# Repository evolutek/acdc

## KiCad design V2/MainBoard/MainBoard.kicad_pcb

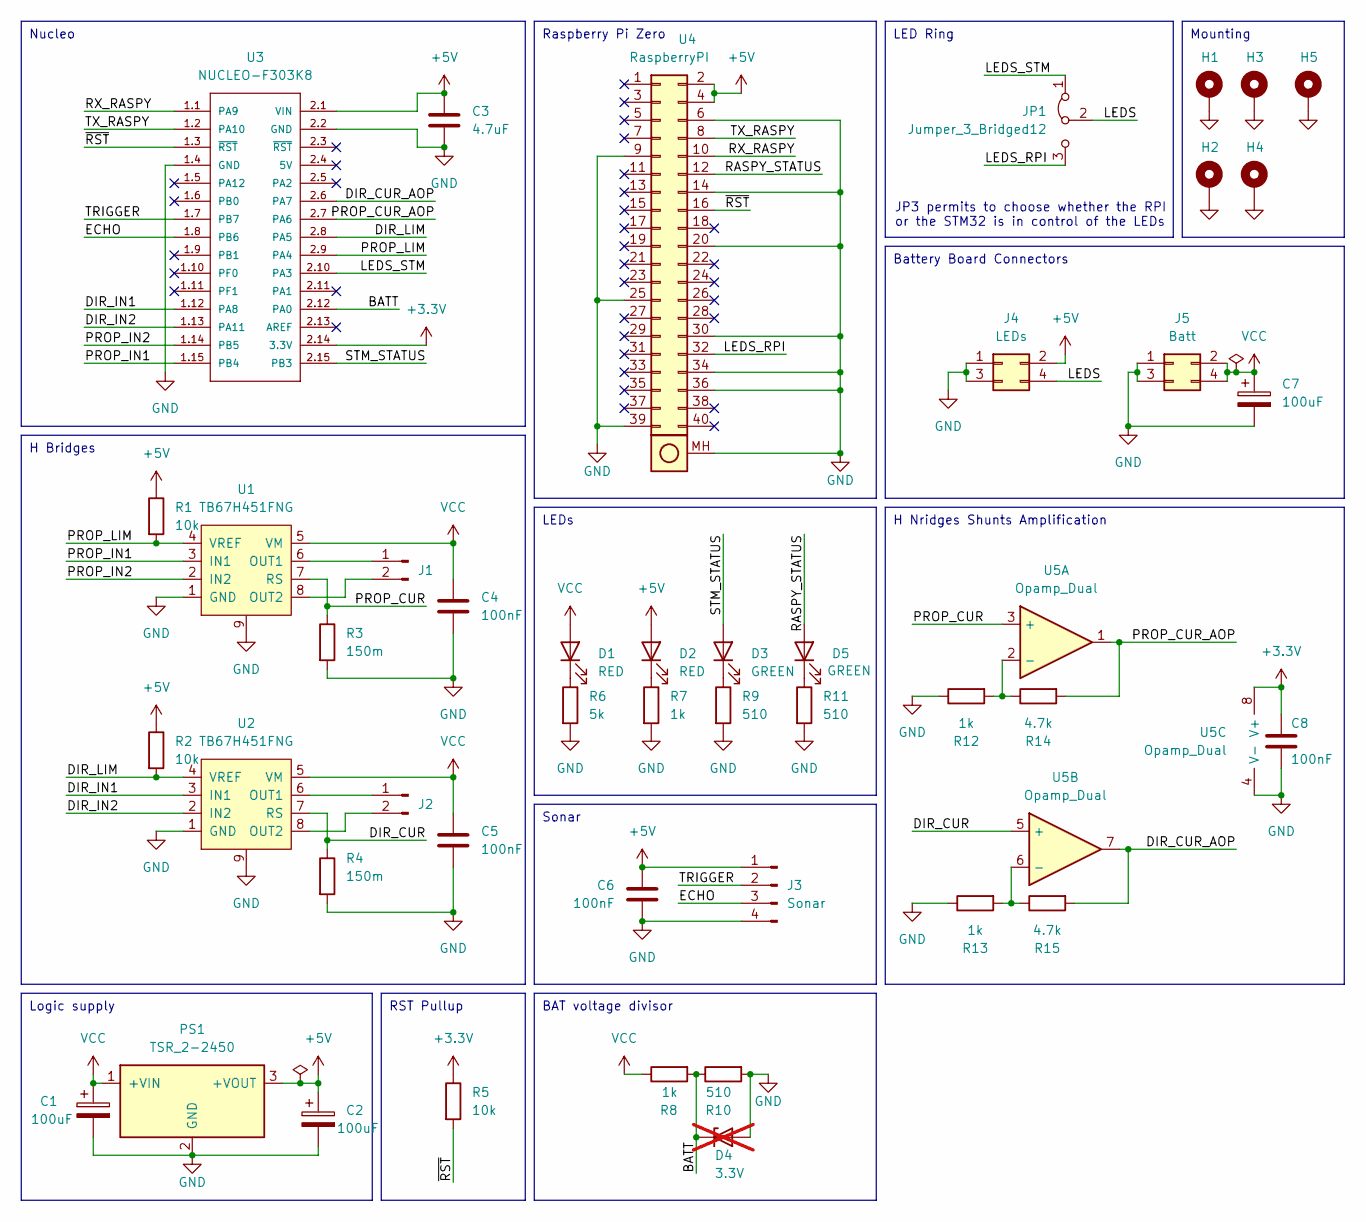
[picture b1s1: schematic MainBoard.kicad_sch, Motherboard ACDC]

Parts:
C1, C7: 100uF; C_Elec_6.3x5.4
C2: 100uF; CP_Elec_6.3x7.7
C3: 4.7uF; C_0603_1608Metric
C4, C5, C6, C8: 100nF; C_0603_1608Metric
D1, D2: RED; LED_0805_2012Metric
D3, D5: GREEN; LED_0805_2012Metric
D4: 3.3V; D_SOD-523; not fitted
H1, H2, H3, H4: MountingHole_Pad; MountingHole_2.5mm_Pad_Via
H5: MountingHole_Pad; WA-SMSI_9774110360
J1, J2: Conn_01x02_Pin; JST_PH_S2B-PH-K_1x02_P2.00mm_Horizontal
J3: Sonar; PinHeader_1x04_P2.54mm_Vertical
J4: LEDs; PinSocket_2x02_P2.54mm_Vertical_SMD
J5: Batt; PinSocket_2x02_P2.54mm_Vertical_SMD
JP1: Jumper_3_Bridged12; PinHeader_1x03_P2.54mm_Vertical
PS1: TSR_2-2450
R1, R2, R5: 10k; R_0603_1608Metric
R3, R4: 150m; R_0805_2012Metric
R6: 5k; R_0603_1608Metric
R7, R8, R12, R13: 1k; R_0603_1608Metric
R9, R10, R11: 510; R_0603_1608Metric
R14, R15: 4.7k; R_0603_1608Metric
U1, U2: TB67H451FNG; HSOP-8-1EP_3.9x4.9mm_P1.27mm_EP2.41x3.1mm_ThermalVias
U3: NUCLEO-F303K8; MODULE_NUCLEO-F303K8
U4: RaspberryPI; Shield_Raspberry_Pi_Zero_W
U5: Opamp_Dual; SOIC-8_3.9x4.9mm_P1.27mm

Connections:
+3.3V: C8.1, R5.1, U3.2.14 (3.3V), U5.8 (V+)
+5V: C2.1, C3.1, C6.1, D2.2 (A), J3.1, J4.2, PS1.3 (+VOUT), R1.1, R2.1, U3.2.1 (VIN), U4.2, U4.4
/BATT: D4.1 (K), R8.2, R10.1, U3.2.12 (PA0)
/DIR_CUR: R4.1, U2.7 (RS), U5.5 (+)
/DIR_CUR_AOP: R15.2, U3.2.6 (PA7), U5.7
/DIR_IN1: U2.3 (IN1), U3.1.12 (PA8)
/DIR_IN2: U2.2 (IN2), U3.1.13 (PA11)
/DIR_LIM: R2.2, U2.4 (VREF), U3.2.8 (PA5)
/ECHO: J3.3, U3.1.8 (PB6)
/LEDS: J4.4, JP1.2 (C)
/LEDS_RPI: JP1.3 (B), U4.32
/LEDS_STM: JP1.1 (A), U3.2.10 (PA3)
/PROP_CUR: R3.1, U1.7 (RS), U5.3 (+)
/PROP_CUR_AOP: R14.2, U3.2.7 (PA6), U5.1
/PROP_IN1: U1.3 (IN1), U3.1.15 (PB4)
/PROP_IN2: U1.2 (IN2), U3.1.14 (PB5)
/PROP_LIM: R1.2, U1.4 (VREF), U3.2.9 (PA4)
/RASPY_STATUS: D5.2 (A), U4.12
/RX_RASPY: U3.1.1 (PA9), U4.10
/STM_STATUS: D3.2 (A), U3.2.15 (PB3)
/TRIGGER: J3.2, U3.1.7 (PB7)
/TX_RASPY: U3.1.2 (PA10), U4.8
/~RST: R5.2, U3.1.3 (~RST), U4.16
GND: C1.2, C2.2, C3.2, C4.2, C5.2, C6.2, C7.2, C8.2, D4.2 (A), H1.1, H2.1, H3.1, H4.1, H5.1, J3.4, J4.1, J4.3, J5.1, J5.3, PS1.2 (GND), R3.2, R4.2, R6.2, R7.2, R9.2, R10.2, R11.2, R12.1, R13.1, U1.1 (GND), U1.9, U2.1 (GND), U2.9, U3.1.4 (GND), U3.2.2 (GND), U4.6, U4.9, U4.14, U4.20, U4.25, U4.30, U4.34, U4.36, U4.39, U4.MH (MountingHoles), U5.4 (V-)
unnamed: D1.1 (K), R6.1
unnamed: D2.1 (K), R7.1
unnamed: D3.1 (K), R9.1
unnamed: D5.1 (K), R11.1
unnamed: J1.1, U1.6 (OUT1)
unnamed: J1.2, U1.8 (OUT2)
unnamed: J2.1, U2.6 (OUT1)
unnamed: J2.2, U2.8 (OUT2)
unnamed: R12.2, R14.1, U5.2 (-)
unnamed: R13.2, R15.1, U5.6 (-)
VCC: C1.1, C4.1, C5.1, C7.1, D1.2 (A), J5.2, J5.4, PS1.1 (+VIN), R8.1, U1.5 (VM), U2.5 (VM)

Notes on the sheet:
Battery Board Connectors
H Bridges
Sonar
Raspberry Pi Zero
Mounting
H Nridges Shunts Amplification
Nucleo
BAT voltage divisor
LED Ring
LEDs
Logic supply
RST Pullup
JP3 permits to choose whether the RPI or the STM32 is in control of the LEDs

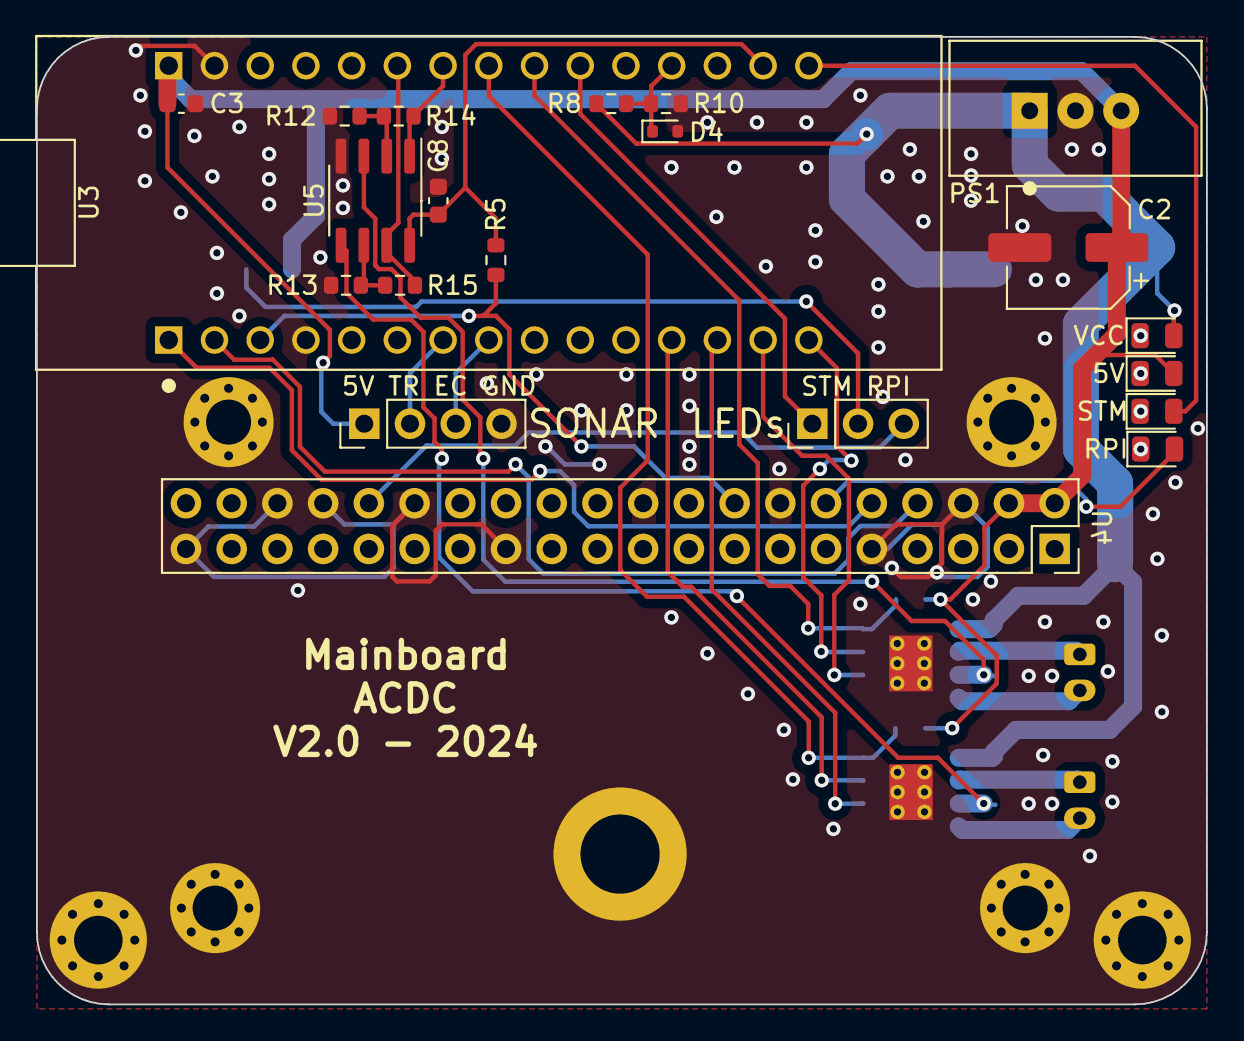
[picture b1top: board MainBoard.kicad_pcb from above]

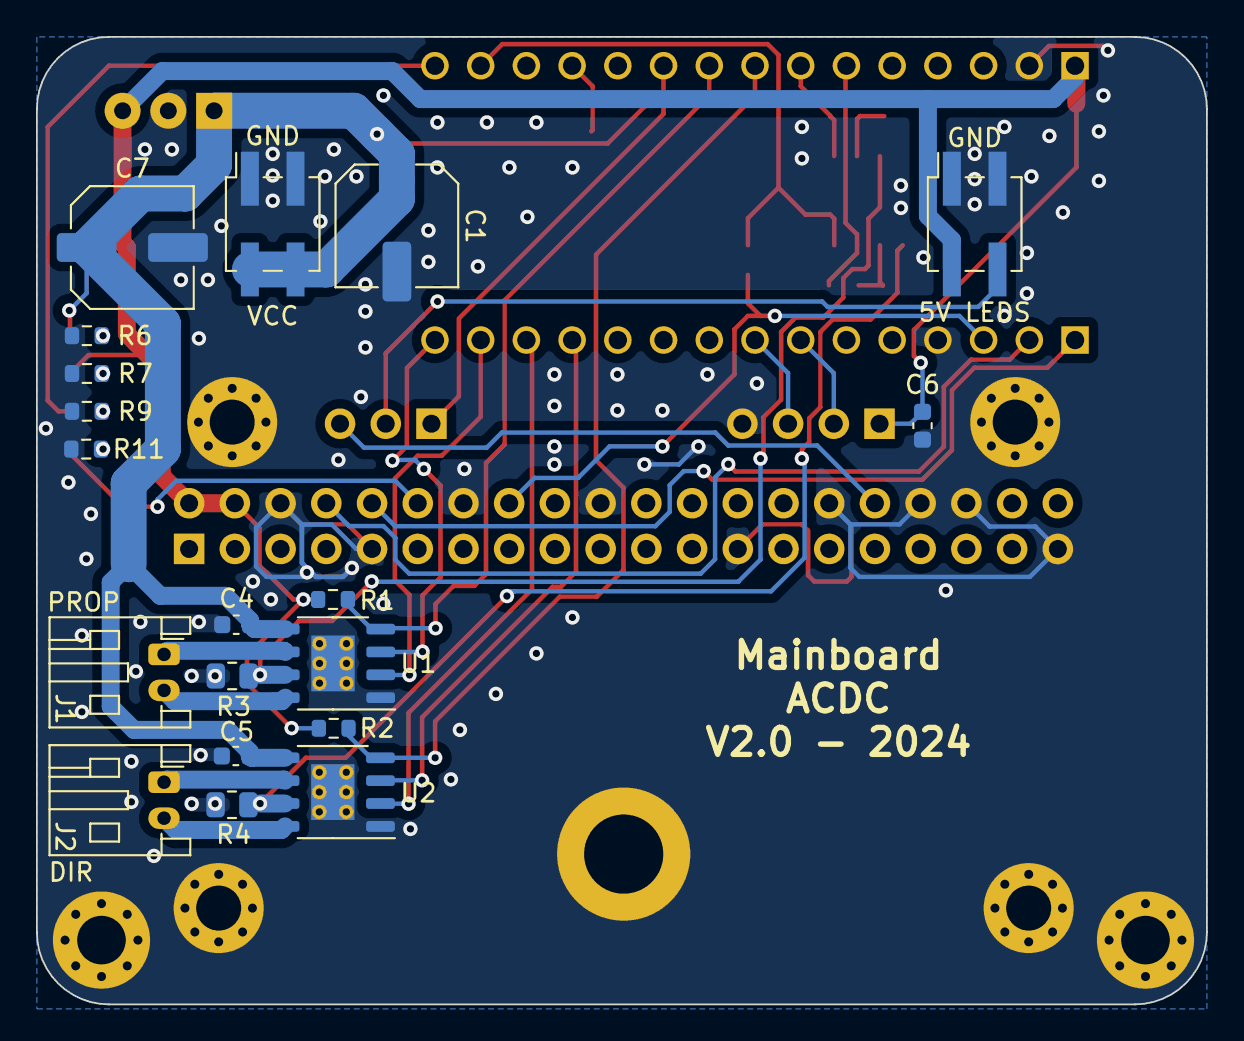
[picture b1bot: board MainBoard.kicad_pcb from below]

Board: 2 copper layers, 65.0 x 53.8 mm, 45 parts (21 on the bottom side), 35 nets.

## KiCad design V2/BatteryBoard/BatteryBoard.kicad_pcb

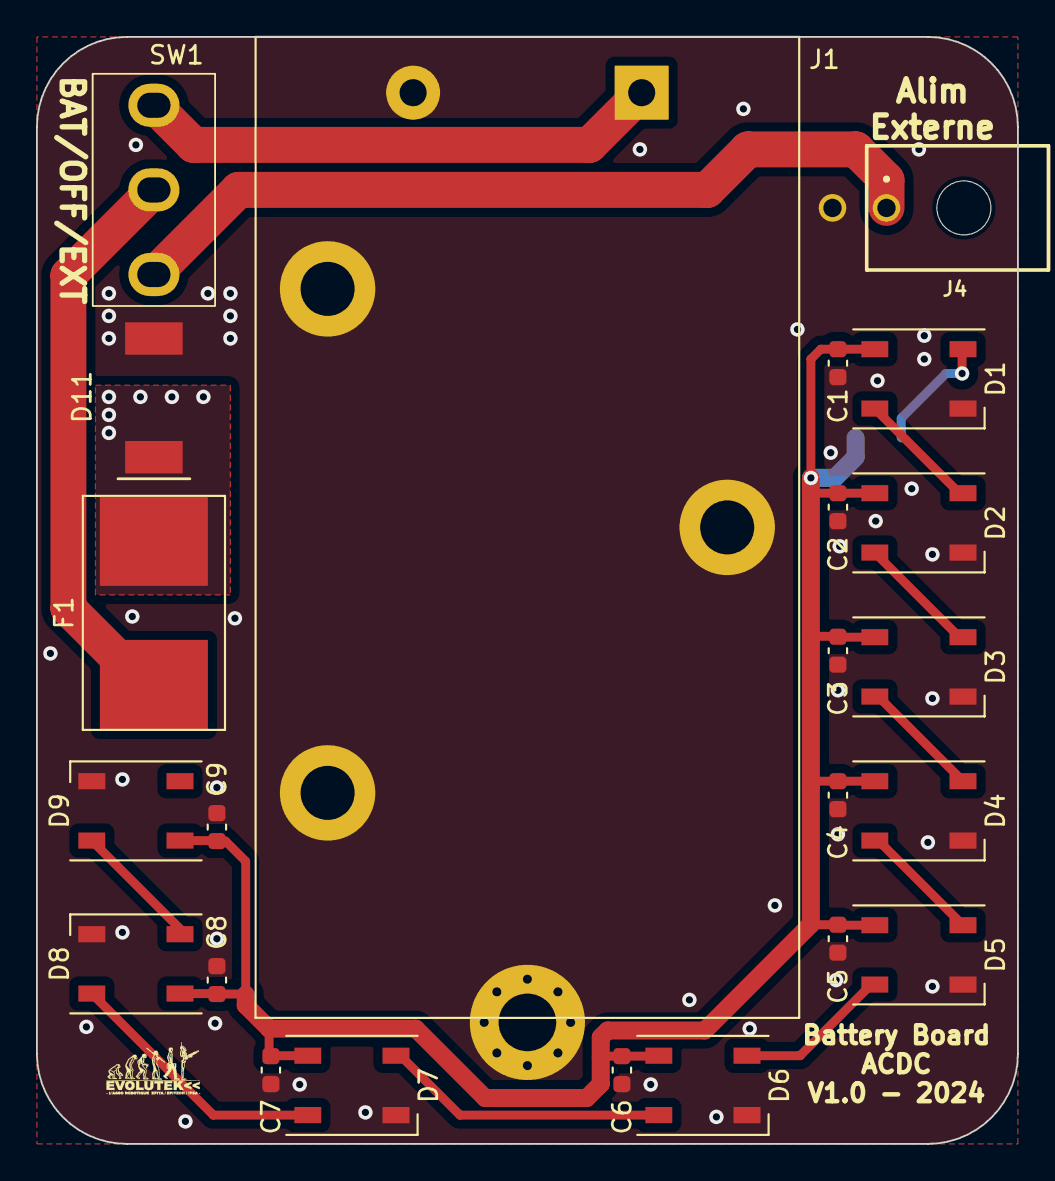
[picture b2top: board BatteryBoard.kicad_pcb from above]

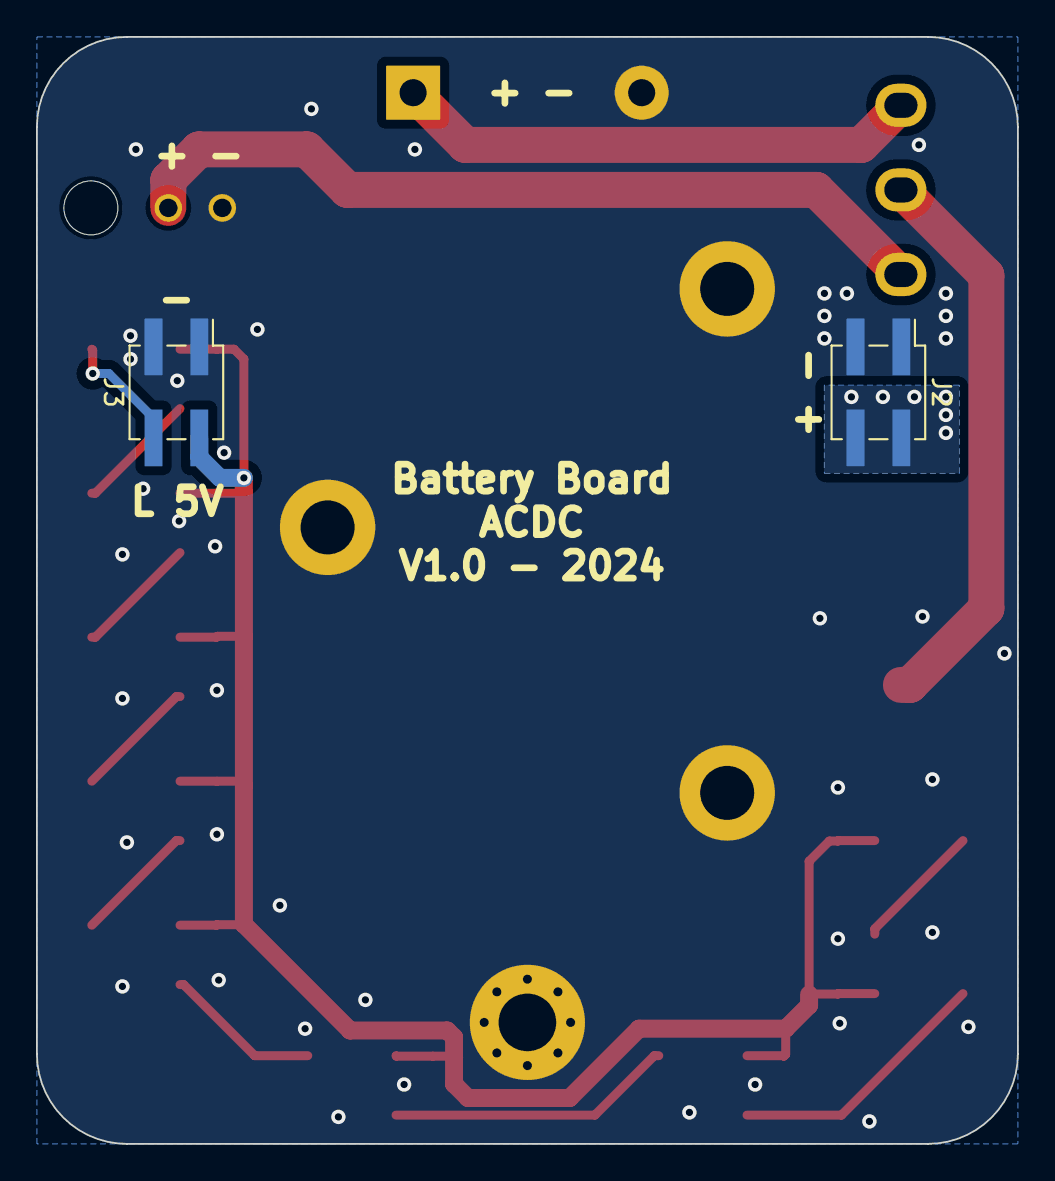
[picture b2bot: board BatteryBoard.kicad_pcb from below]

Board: 2 copper layers, 54.5 x 61.5 mm, 26 parts (2 on the bottom side), 15 nets.

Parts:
C1, C2, C3, C4, C5, C6, C7, C8, C9: 100nF; C_0603_1608Metric
D1, D2, D3, D4, D5, D6, D7, D8, D9: WS2812B; LED_WS2812B_PLCC4_5.0x5.0mm_P3.2mm
D11: D; DO-214AB
F1: Fuse; 0031.7701.11
H1: MountingHole_Pad; MountingHole_3.2mm_M3_Pad_Via
J1: 9V Battery; BatteryHolder_Eagle_12BH611-GR-Modified
J2, J3: Conn_02x02_Odd_Even; PinHeader_2x02_P2.54mm_Vertical_SMD
J4: Aux Alim; 66200221022
SW1: SW_SPDT_MSM; Power Switch RS SPDT

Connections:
+5V: C1.1, C2.1, C3.1, C4.1, C5.1, C6.1, C7.1, C8.1, C9.1, D1.1 (VDD), D2.1 (VDD), D3.1 (VDD), D4.1 (VDD), D5.1 (VDD), D6.1 (VDD), D7.1 (VDD), D8.1 (VDD), D9.1 (VDD), J3.2
/LEDS: D1.4 (DIN), J3.4
/LEDS_LTR: D5.2 (DOUT), D6.4 (DIN)
GND: C1.2, C2.2, C3.2, C4.2, C5.2, C6.2, C7.2, C8.2, C9.2, D1.3 (VSS), D2.3 (VSS), D3.3 (VSS), D4.3 (VSS), D5.3 (VSS), D6.3 (VSS), D7.3 (VSS), D8.3 (VSS), D9.3 (VSS), D11.2 (A), H1.1, J1.2, J1.MP (MountPin), J2.1, J2.3, J3.1, J3.3, J4.2
unnamed: D1.2 (DOUT), D2.4 (DIN)
unnamed: D2.2 (DOUT), D3.4 (DIN)
unnamed: D3.2 (DOUT), D4.4 (DIN)
unnamed: D4.2 (DOUT), D5.4 (DIN)
unnamed: D6.2 (DOUT), D7.4 (DIN)
unnamed: D7.2 (DOUT), D8.4 (DIN)
unnamed: D8.2 (DOUT), D9.4 (DIN)
unnamed: F1.1, SW1.2
unnamed: J1.1, SW1.3
unnamed: J4.1, SW1.1
VCC: D11.1 (K), F1.2, J2.2, J2.4

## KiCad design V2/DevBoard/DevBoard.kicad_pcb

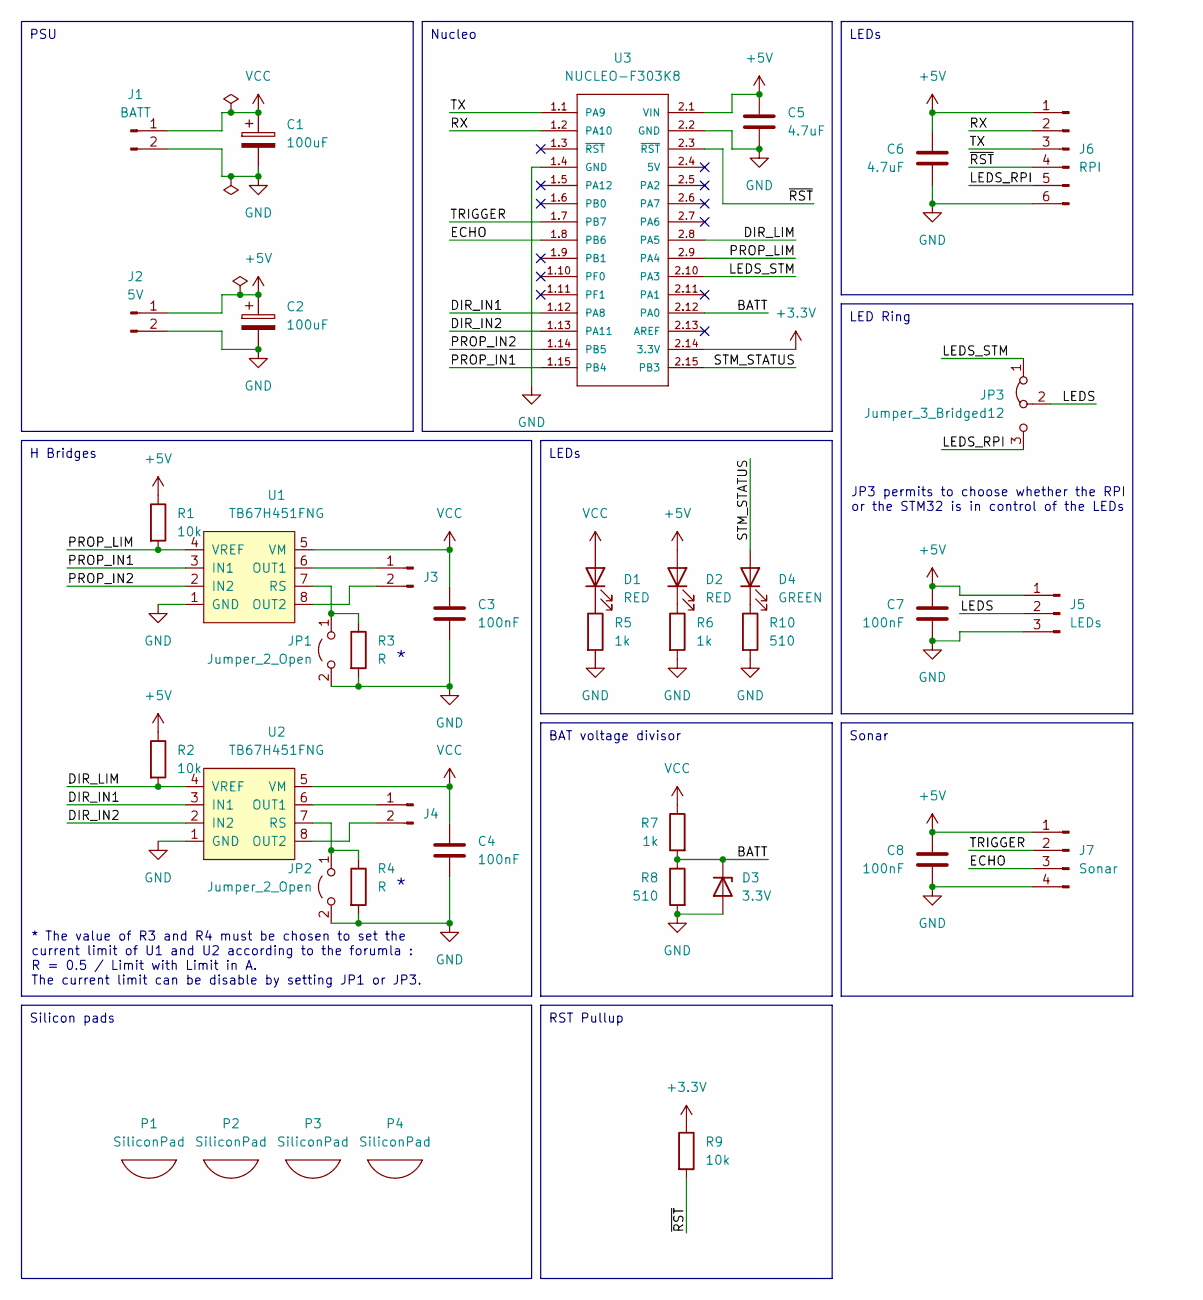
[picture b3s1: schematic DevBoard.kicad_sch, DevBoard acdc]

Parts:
C1, C2: 100uF; CP_Elec_6.3x7.7
C3, C4, C7, C8: 100nF; C_0603_1608Metric
C5, C6: 4.7uF; C_0603_1608Metric
D1, D2: RED; LED_0805_2012Metric
D3: 3.3V; D_SOD-523
D4: GREEN; LED_0805_2012Metric
J1: BATT; 66200221022
J2: 5V; 66200221022
J3, J4: Conn_01x02_Pin; PinHeader_1x02_P2.54mm_Vertical
J5: LEDs; PinHeader_1x03_P2.54mm_Vertical
J6: RPI; PinHeader_1x06_P2.54mm_Vertical
J7: Sonar; PinHeader_1x04_P2.54mm_Vertical
JP1, JP2: Jumper_2_Open; SolderJumper-2_P1.3mm_Open_TrianglePad1.0x1.5mm
JP3: Jumper_3_Bridged12; PinHeader_1x03_P2.54mm_Vertical
P1, P2, P3, P4: SiliconPad; Silicon Pad 6x2mm
R1, R2, R9: 10k; R_0603_1608Metric
R3, R4: R; R_0603_1608Metric
R5, R6, R7: 1k; R_0603_1608Metric
R8, R10: 510; R_0603_1608Metric
U1, U2: TB67H451FNG; HSOP-8-1EP_3.9x4.9mm_P1.27mm_EP2.41x3.1mm_ThermalVias
U3: NUCLEO-F303K8; MODULE_NUCLEO-F303K8

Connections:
+3.3V: R9.1, U3.2.14 (3.3V)
+5V: C2.1, C5.1, C6.1, C7.1, C8.1, D2.2 (A), J2.1, J5.1, J6.1, J7.1, R1.1, R2.1, U3.2.1 (VIN)
/BATT: D3.1 (K), R7.2, R8.1, U3.2.12 (PA0)
/DIR_IN1: U2.3 (IN1), U3.1.12 (PA8)
/DIR_IN2: U2.2 (IN2), U3.1.13 (PA11)
/DIR_LIM: R2.2, U2.4 (VREF), U3.2.8 (PA5)
/ECHO: J7.3, U3.1.8 (PB6)
/LEDS: J5.2, JP3.2 (C)
/LEDS_RPI: J6.5, JP3.3 (B)
/LEDS_STM: JP3.1 (A), U3.2.10 (PA3)
/PROP_IN1: U1.3 (IN1), U3.1.15 (PB4)
/PROP_IN2: U1.2 (IN2), U3.1.14 (PB5)
/PROP_LIM: R1.2, U1.4 (VREF), U3.2.9 (PA4)
/RX: J6.2, U3.1.2 (PA10)
/STM_STATUS: D4.2 (A), U3.2.15 (PB3)
/TRIGGER: J7.2, U3.1.7 (PB7)
/TX: J6.3, U3.1.1 (PA9)
/~RST: J6.4, R9.2, U3.2.3 (~RST)
GND: C1.2, C2.2, C3.2, C4.2, C5.2, C6.2, C7.2, C8.2, D3.2 (A), J1.2, J2.2, J5.3, J6.6, J7.4, JP1.2 (B), JP2.2 (B), R3.2, R4.2, R5.2, R6.2, R8.2, R10.2, U1.1 (GND), U2.1 (GND), U3.1.4 (GND), U3.2.2 (GND)
unnamed: D1.1 (K), R5.1
unnamed: D2.1 (K), R6.1
unnamed: D4.1 (K), R10.1
unnamed: J3.1, U1.6 (OUT1)
unnamed: J3.2, U1.8 (OUT2)
unnamed: J4.1, U2.6 (OUT1)
unnamed: J4.2, U2.8 (OUT2)
unnamed: JP1.1 (A), R3.1, U1.7 (RS)
unnamed: JP2.1 (A), R4.1, U2.7 (RS)
VCC: C1.1, C3.1, C4.1, D1.2 (A), J1.1, R7.1, U1.5 (VM), U2.5 (VM)

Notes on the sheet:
LEDs
H Bridges
Sonar
PSU
Silicon pads
Nucleo
BAT voltage divisor
LED Ring
RST Pullup
JP3 permits to choose whether the RPI or the STM32 is in control of the LEDs
* The value of R3 and R4 must be chosen to set the current limit of U1 and U2 according to the forumla : R = 0.5 / Limit with Limit in A. The current limit can be disable by setting JP1 or JP3.

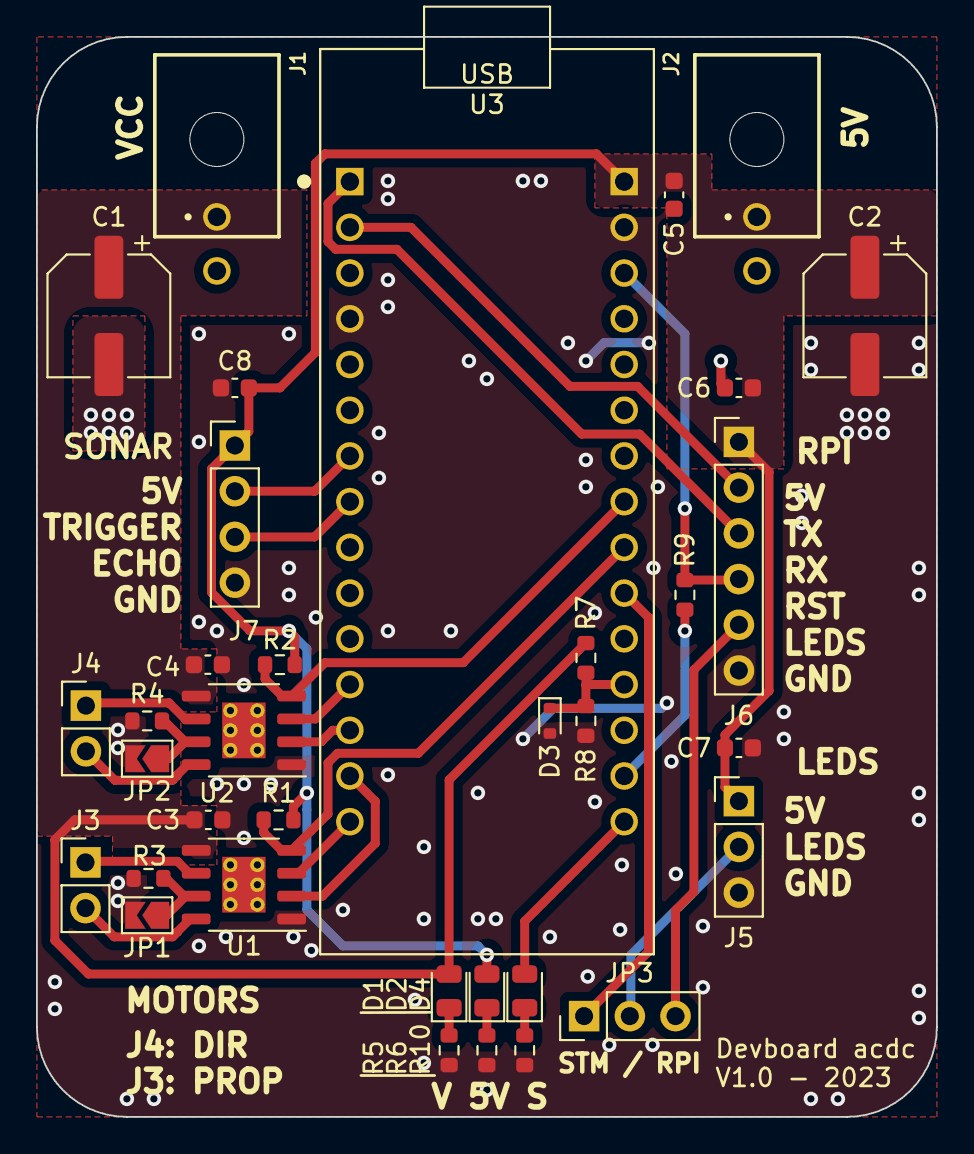
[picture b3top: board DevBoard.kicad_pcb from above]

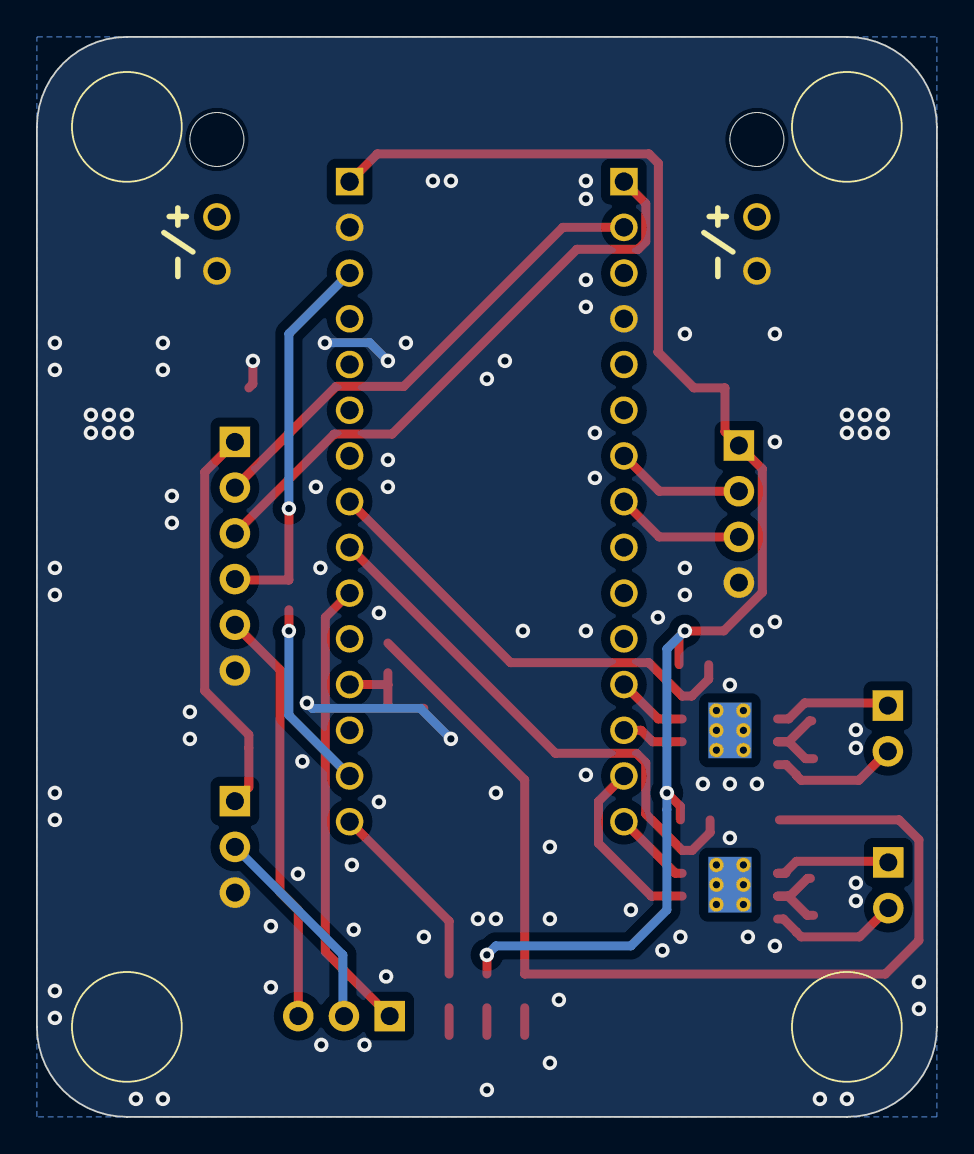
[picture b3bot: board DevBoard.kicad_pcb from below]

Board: 2 copper layers, 50.0 x 60.0 mm, 39 parts (4 on the bottom side), 29 nets.

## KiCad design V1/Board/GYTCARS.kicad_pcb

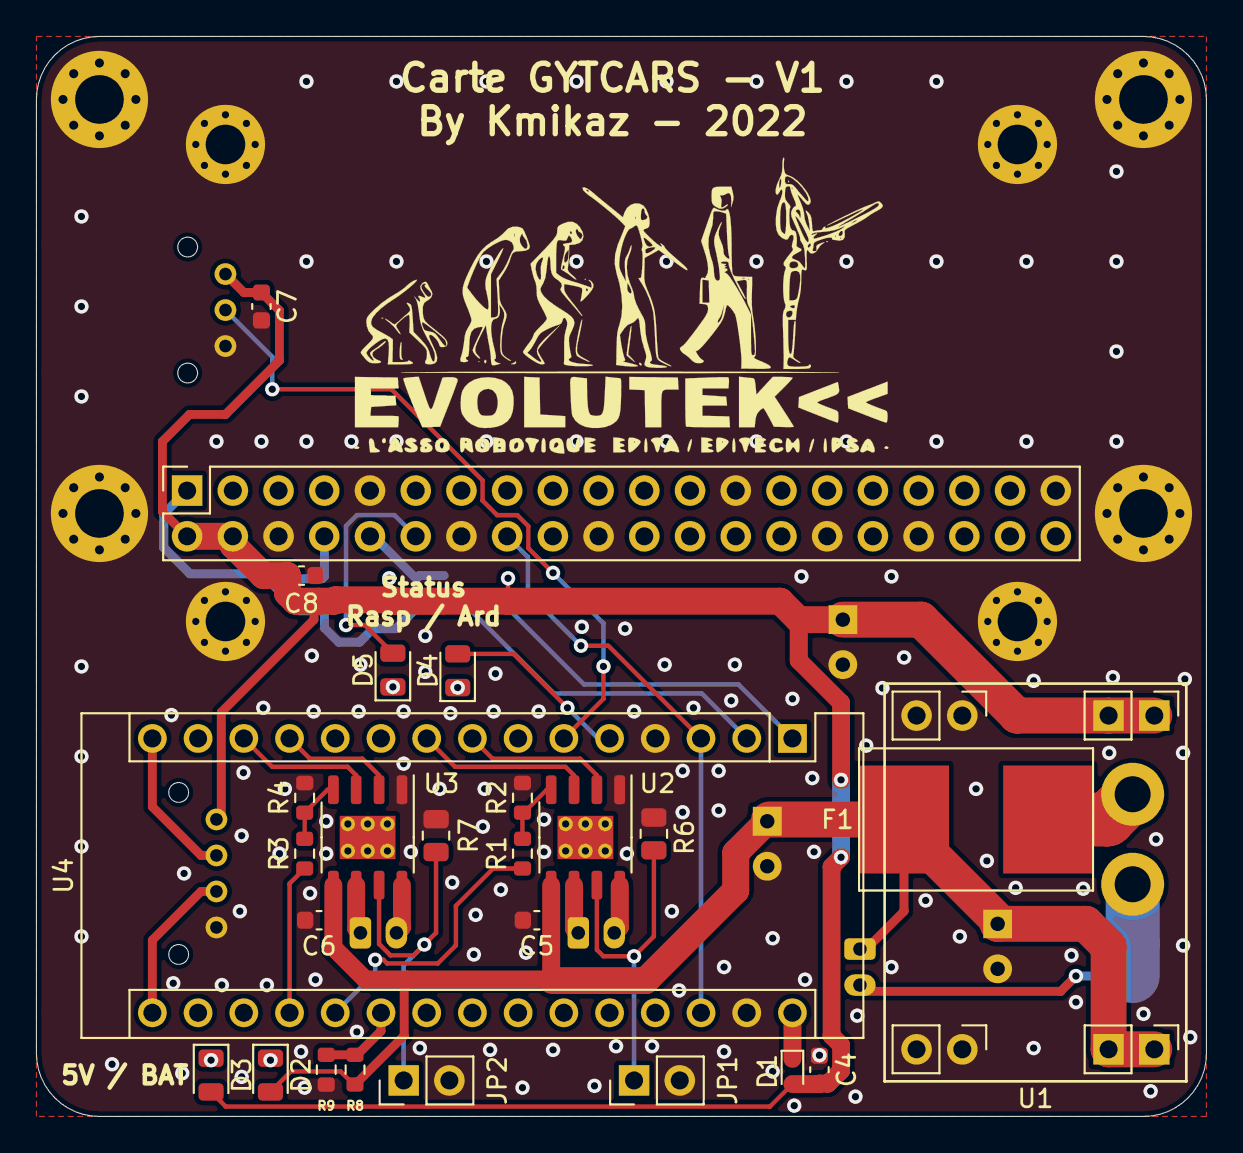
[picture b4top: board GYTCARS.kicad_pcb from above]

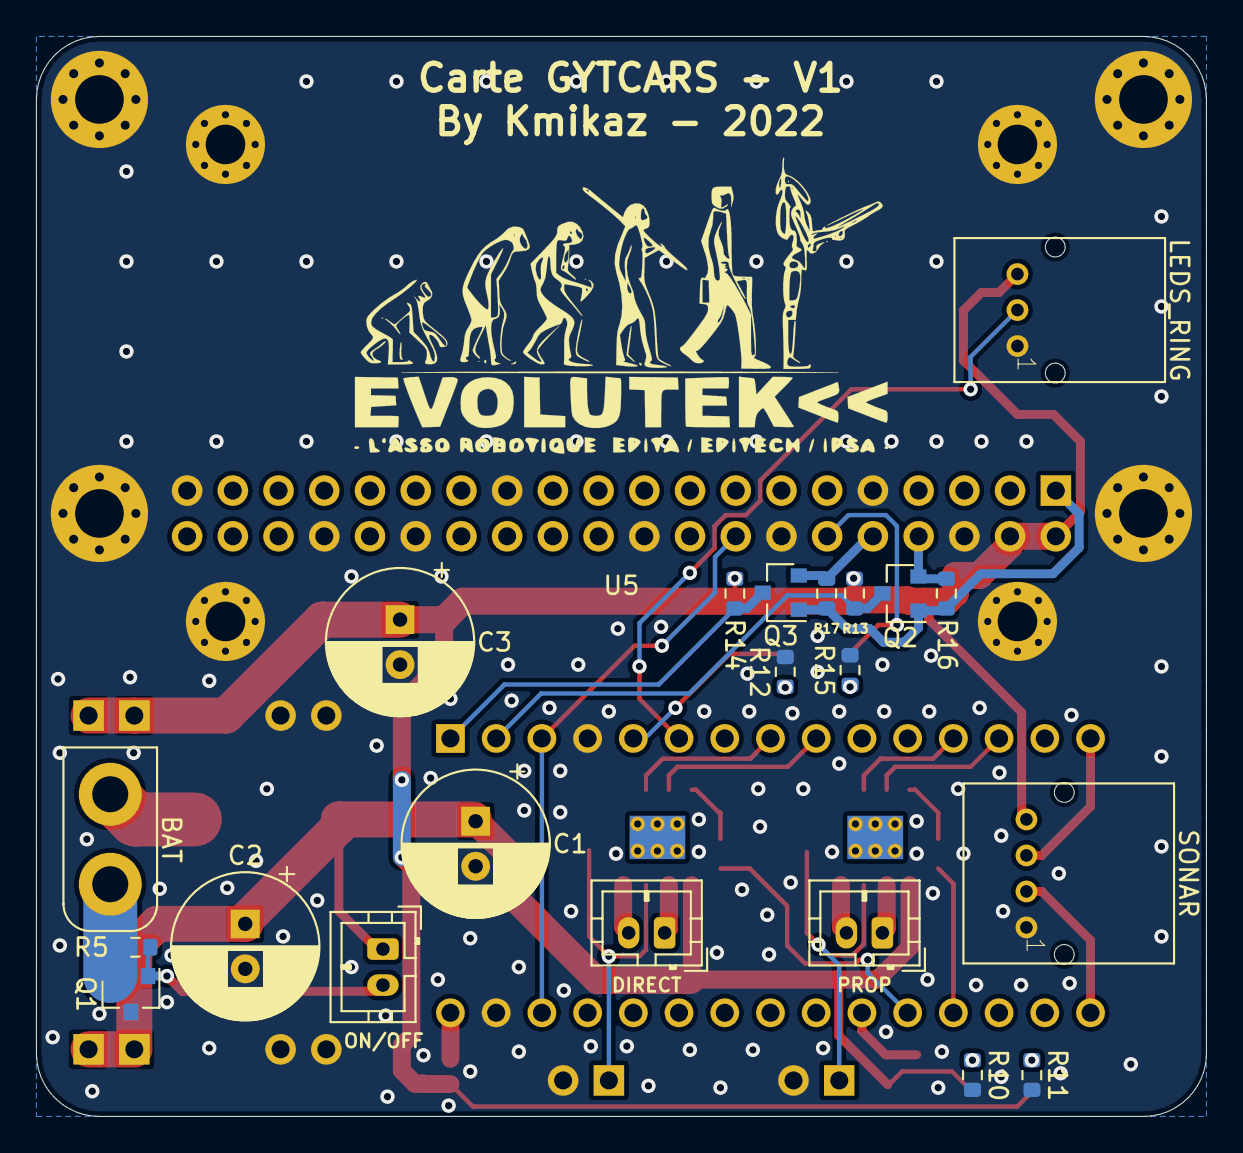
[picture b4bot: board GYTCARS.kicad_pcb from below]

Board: 2 copper layers, 65.0 x 60.0 mm, 51 parts (22 on the bottom side), 37 nets.

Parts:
BAT: XT30 Male; XT30
C1, C2, C3: 220uF; CP_Radial_D8.0mm_P2.50mm
C4, C5, C6, C7, C8: 4.7uF; C_0603_1608Metric
D1: D; D_SOD-523
D2, D3: RED; LED_0805_2012Metric
D4, D5: GREEN; LED_0805_2012Metric
DIRECT: JST PH 2; JST_PH_B2B-PH-K_1x02_P2.00mm_Vertical
F1: Fuse; 0031.7701.11
H1, H2, H3, H4: MountingHole_Pad; MountingHole_2.2mm_M2_Pad_Via
JP1, JP2: SolderJumper_2_Open; PinHeader_1x02_P2.54mm_Vertical
LEDS_RING: JST PA 3; S03B-PASK
ON/OFF: JST PH 2; JST_PH_B2B-PH-K_1x02_P2.00mm_Vertical
PROP: JST PH 2; JST_PH_B2B-PH-K_1x02_P2.00mm_Vertical
Q1, Q2, Q3: Q_NMOS_GSD; SOT-23
R1, R3: 150; R_0603_1608Metric
R2, R4: 510; R_0603_1608Metric
R5, R8, R9, R13, R14, R16, R17: 10K; R_0603_1608Metric
R6, R7: 0.15; R_0805_2012Metric
R10, R11, R12, R15: 1K; R_0603_1608Metric
SONAR: JST PA 4; S04B-PASK
U1: MP1584EB; MP1584EN
U2, U3: TB67H451FNG; HSOP-8-1EP_3.9x4.9mm_P1.27mm_EP2.41x3.1mm_ThermalVias
U4: Arduino_Nano_v3.x; ArduinoNano
U5: RaspberryPI; Shield_Raspberry_Pi_Zero_W

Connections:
+3V3: Q2.1, Q3.1, R16.1, R17.1, U5.1
+5V: C3.1, C4.1, C7.1, C8.1, D1.2, D3.2, LEDS_RING.1, R13.1, R14.1, SONAR.1, U1.3, U5.2, U5.4
+BATT: C1.1, C2.1, C5.1, C6.1, D2.2, F1.1, ON/OFF.1, R8.1, U1.1, U2.5, U3.5
/ECHO_SONAR: SONAR.3, U4.16
/LEDS_RING: LEDS_RING.2, U4.6
/LIMIT_DIRECT: R1.1, U4.20
/LIMIT_PROP: R3.1, U4.19
/ON: ON/OFF.2, Q1.1, R5.2
/PWM1_DIRECT: U2.3, U4.9
/PWM1_PROP: U3.3, U4.13
/PWM2_DIRECT: U2.2, U4.8
/PWM2_PROP: U3.2, U4.12
/RX_ARDUINO: Q2.3, R13.2, U4.2
/RX_RASPY: Q3.2, R17.2, U5.10
/STATUS_ARDUINO: D4.2, U4.5
/STATUS_RASPY: D5.2, U5.12
/TRIGGER_SONAR: SONAR.2, U4.15
/TX_ARDUINO: Q3.3, R14.2, U4.1
/TX_RASPY: Q2.2, R16.2, U5.8
/~RST_ARDUINO: U4.3, U4.28, U5.16
GND: C1.2, C2.2, C3.2, C4.2, C5.2, C6.2, C7.2, C8.2, H1.1, H2.1, H3.1, H4.1, JP1.2, JP2.2, LEDS_RING.3, Q1.3, R2.2, R4.2, R6.2, R7.2, R9.2, R10.2, R11.2, R12.2, R15.2, SONAR.4, U1.2, U1.4, U2.1, U3.1, U4.4, U4.29, U5.6, U5.9, U5.14, U5.20, U5.25, U5.30, U5.34, U5.39, U5.MH
unnamed: BAT.1, F1.2
unnamed: BAT.2, Q1.2, R5.1
unnamed: D1.1, U4.30
unnamed: D2.1, R10.1
unnamed: D3.1, R11.1
unnamed: D4.1, R12.1
unnamed: D5.1, R15.1
unnamed: DIRECT.1, U2.6
unnamed: DIRECT.2, U2.8
unnamed: JP1.1, R6.1, U2.7
unnamed: JP2.1, R7.1, U3.7
unnamed: PROP.1, U3.6
unnamed: PROP.2, U3.8
unnamed: R1.2, R2.1, U2.4
unnamed: R3.2, R4.1, U3.4
unnamed: R8.2, R9.1, U4.21

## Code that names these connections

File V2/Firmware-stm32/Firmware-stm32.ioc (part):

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Mcu.Name=STM32F303K(6-8)Tx
Mcu.Package=LQFP32
Mcu.UserName=STM32F303K8Tx
PA0.GPIOParameters=GPIO_Label
PA0.GPIO_Label=BATT
PA0.Mode=IN1-Single-Ended
PA0.Signal=ADC1_IN1
PA10.GPIOParameters=GPIO_Label
PA10.GPIO_Label=RX
PA10.Mode=Asynchronous
PA10.Signal=USART1_RX
PA11.GPIOParameters=GPIO_Label
PA11.GPIO_Label=DIR_IN2
PA11.Signal=S_TIM1_CH4
PA13.GPIOParameters=GPIO_Label
PA13.GPIO_Label=SWDIO
PA13.Mode=Serial_Wire
PA13.Signal=SYS_JTMS-SWDIO
PA14.GPIOParameters=GPIO_Label
PA14.GPIO_Label=SWCLK
PA14.Mode=Serial_Wire
PA14.Signal=SYS_JTCK-SWCLK
PA15.GPIOParameters=GPIO_Label
PA15.GPIO_Label=VCP_RX
PA15.Mode=Asynchronous
PA15.Signal=USART2_RX
PA2.GPIOParameters=GPIO_Label
PA2.GPIO_Label=VCP_TX
PA2.Mode=Asynchronous
PA2.Signal=USART2_TX
PA3.GPIOParameters=GPIO_Label
PA3.GPIO_Label=LEDS
PA3.Signal=S_TIM2_CH4
PA4.GPIOParameters=GPIO_Label
PA4.GPIO_Label=PROP_LIM
PA4.Signal=COMP_DAC11_group
PA5.GPIOParameters=GPIO_Label
PA5.GPIO_Label=DIR_LIM
PA5.Signal=COMP_DAC12_group
PA8.GPIOParameters=GPIO_Label
PA8.GPIO_Label=DIR_IN1
PA8.Signal=S_TIM1_CH1
PA9.GPIOParameters=GPIO_Label
PA9.GPIO_Label=TX
PA9.Mode=Asynchronous
PA9.Signal=USART1_TX
PB3.GPIOParameters=GPIO_Label
PB3.GPIO_Label=STATUS_LED
PB3.Signal=GPIO_Output
PB4.GPIOParameters=GPIO_Label
PB4.GPIO_Label=PROP_IN1
PB4.Signal=S_TIM3_CH1
PB5.GPIOParameters=GPIO_Label
PB5.GPIO_Label=PROP_IN2
PB5.Signal=S_TIM3_CH2
PB6.GPIOParameters=GPIO_Label
PB6.GPIO_Label=ECHO
PB6.Signal=GPXTI6
PB7.GPIOParameters=GPIO_Label
PB7.GPIO_Label=TRIGGER
PB7.Signal=GPIO_Input
RCC.HSEPLLFreq_Value=8000000
RCC.HSE_VALUE=8000000
RCC.SYSCLKFreq_VALUE=64000000
RCC.SYSCLKSourceVirtual=RCC_SYSCLKSOURCE_PLLCLK
board=NUCLEO-F303K8
boardIOC=true

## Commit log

2022-06-15 wip schematics
2022-06-17 [ADD] Controller file with basic handling of the controller inputs [ADD] .gitignore file
2022-06-17 [FIX] Left a useless line causing a crash, also added the print of the script version
2022-06-21 First version of the board
2022-06-24 Wip Arduino Firmware
2022-06-24 [ADD] More handling for future communication with raspi 0
2022-06-26 Add get voltage command
2022-06-27 Manage motor current limit and fix some minor bugs
2022-06-27 [REM] Error when vibrtion occurs on raspi0
2022-06-27 [FIX] Script Version
2022-06-27 [ADD] epoch of protocol
2022-06-27 [ADD] try setup
2022-06-27 Minor fixes
2022-06-27 [ADD] change file for enum
2022-06-27 [FIX] correction of return
2022-06-27 [FIX] read
2022-06-27 [FIX] enum
2022-06-27 [ADD] cmd: set_angle ping
2022-06-27 [FIX] del angle enum
2022-06-27 [FIX] name of enum
2022-06-27 [ADD] clean controller.py
2022-06-27 Working direction and remove Watchdog
2022-06-27 [ADD] agent for cars
2022-06-27 [ADD] client and server part
2022-06-28 Fix few things
2022-06-28 First version of the mechanical improvements of the car
2022-06-28 [ADD] acceleration
2022-06-28 [ADD] test for accelaration
2022-06-28 [FIX] acceleration
2022-06-28 [FIX] problem import
2023-09-23 Put V1 in subfolder
2023-09-23 WIP devboard for V2
2023-09-25 Add STM32 Firmware
2023-09-25 WIP DevBoard
2023-10-06 Devboard completed
2023-10-06 Fix mapping in stm32 project
2023-10-06 WIP MainBoard schematics
2023-10-21 Convert DevBaord into MainBoard
2023-10-22 initial work on the main board
2023-10-31 routing progress
2023-11-01 Fix screw holes position
2023-11-01 Move connectors and make a 2D sketch for the holes
2023-11-02 Update MainBoard placement
2023-11-02 Need to fix gitignore
2023-11-02 Battery Board V1.0
2023-11-03 done
    needs cleanup and audit
2023-11-03 enhanced motor driver heat dissipation
2023-11-03 Change alim externe conenctor
2023-11-05 Improve MainBoard
2023-11-06 Fix Battery Board
2023-11-06 Fix Main Board
2023-11-12 Minor fix of the silkscreen
2023-12-07 Add code base
2023-12-07 Oups, remove submodule for directory
2023-12-08 Update OpenCV Formation
2023-12-08 Haaaaaa
2023-12-13 Fix WebRTC server ugly exit
2023-12-14 Add config file and begin demo
2023-12-14 Add execution permission to run.sh script
2023-12-14 Fix run
2023-12-14 Working example
2023-12-15 Improve readme
2023-12-15 Little refactoring and add setup function
2023-12-15 Add RPI clone scripts
2023-12-15 [ADD] executable to .sh [FIX] uncomment line 32 for write
2023-12-15 Add Workshop folder
2023-12-15 Remove answer LOL XD
2023-12-15 Disable OpenCV
2023-12-15 Add comments
2023-12-15 Add comments 2
